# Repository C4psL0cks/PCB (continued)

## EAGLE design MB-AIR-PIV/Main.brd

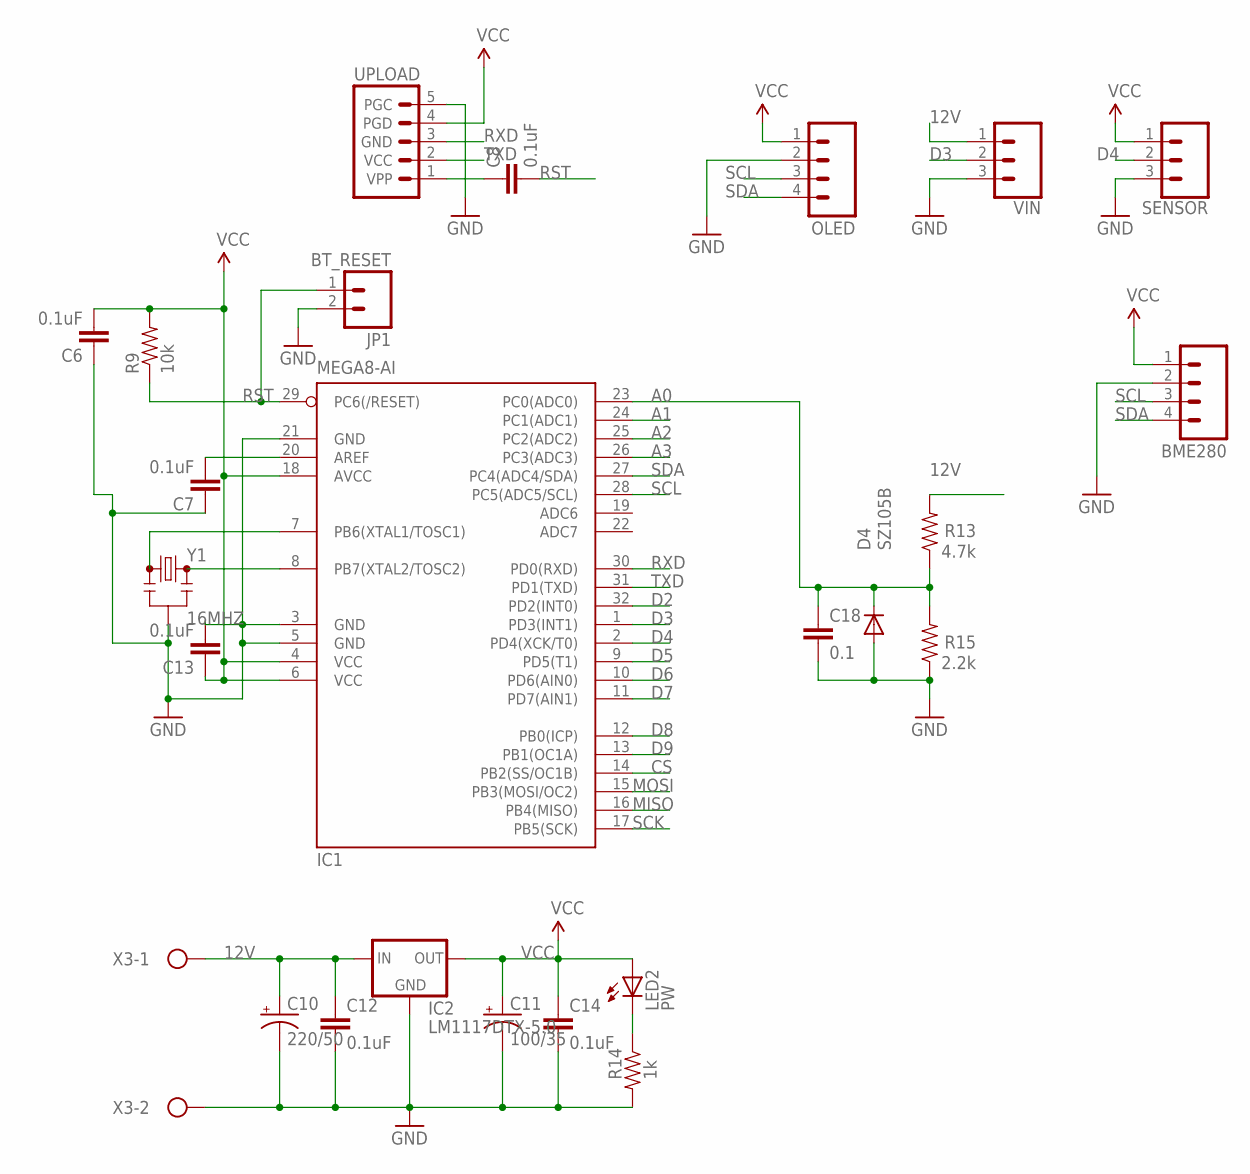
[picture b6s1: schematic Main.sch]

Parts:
BME280: M04PTH; 1X04
C6, C7, C8, C12, C13, C14: 0.1uF; 0805
C10: 220/50; 153CLV-1010
C11: 100/35; 153CLV-0605
C18: 0.1; 0805
D4: SZ105B; DO-214AC
IC1: MEGA8-AI; TQFP32-08
IC2: LM1117DTX-5.0; TO252
JP1: BT_RESET; 1X02
LED2: PW; LED3MM
OLED: M04PTH; 1X04
R9: 10k; 0805
R13: 4.7k; 0805
R14: 1k; 0805
R15: 2.2k; 0805
SENSOR: CONN_03JST-PTH-VERT; JST-3-PTH-VERT
UPLOAD: PIC_ICSP_MINI_5_PIN
VIN: CONN_03JST-PTH-VERT; JST-3-PTH-VERT
X3: RELAY1; W237-102
Y1: 16MHZ; RESONATOR-SMD

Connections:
12V: C10.+, C12.1, IC2.2 (IN), R13.2, VIN.1, X3.1
A0: C18.1, D4.C, IC1.23 (PC0(ADC0)), R13.1, R15.2
A1: IC1.24 (PC1(ADC1))
A2: IC1.25 (PC2(ADC2))
A3: IC1.26 (PC3(ADC3))
CS: IC1.14 (PB2(SS/OC1B))
D2: IC1.32 (PD2(INT0))
D3: IC1.1 (PD3(INT1)), VIN.2
D4: IC1.2 (PD4(XCK/T0)), SENSOR.2
D5: IC1.9 (PD5(T1))
D6: IC1.10 (PD6(AIN0))
D7: IC1.11 (PD7(AIN1))
D8: IC1.12 (PB0(ICP))
D9: IC1.13 (PB1(OC1A))
GND: BME280.2, C6.1, C7.1, C10.-, C11.-, C12.2, C13.2, C14.2, C18.2, D4.A, IC1.3 (GND), IC1.5 (GND), IC1.21 (GND), IC2.1 (GND), JP1.2, OLED.2, R14.2, R15.1, SENSOR.3, UPLOAD.5 (PGC), VIN.3, X3.2, Y1.2
MISO: IC1.16 (PB4(MISO))
MOSI: IC1.15 (PB3(MOSI/OC2))
unnamed: IC1.8 (PB7(XTAL2/TOSC2)), Y1.3
unnamed: IC1.7 (PB6(XTAL1/TOSC1)), Y1.1
unnamed: C7.2, IC1.20 (AREF)
unnamed: C8.1, UPLOAD.1 (VPP)
unnamed: LED2.K (C), R14.1
RST: C8.2, IC1.29 (PC6(/RESET)), JP1.1, R9.1
RXD: IC1.30 (PD0(RXD)), UPLOAD.3 (GND)
SCK: IC1.17 (PB5(SCK))
SCL: BME280.3, IC1.28 (PC5(ADC5/SCL)), OLED.3
SDA: BME280.4, IC1.27 (PC4(ADC4/SDA)), OLED.4
TXD: IC1.31 (PD1(TXD)), UPLOAD.2 (VCC)
VCC: BME280.1, C6.2, C11.+, C13.1, C14.1, IC1.4 (VCC), IC1.6 (VCC), IC1.18 (AVCC), IC2.TAB (OUT), LED2.A, OLED.1, R9.2, SENSOR.1, UPLOAD.4 (PGD)

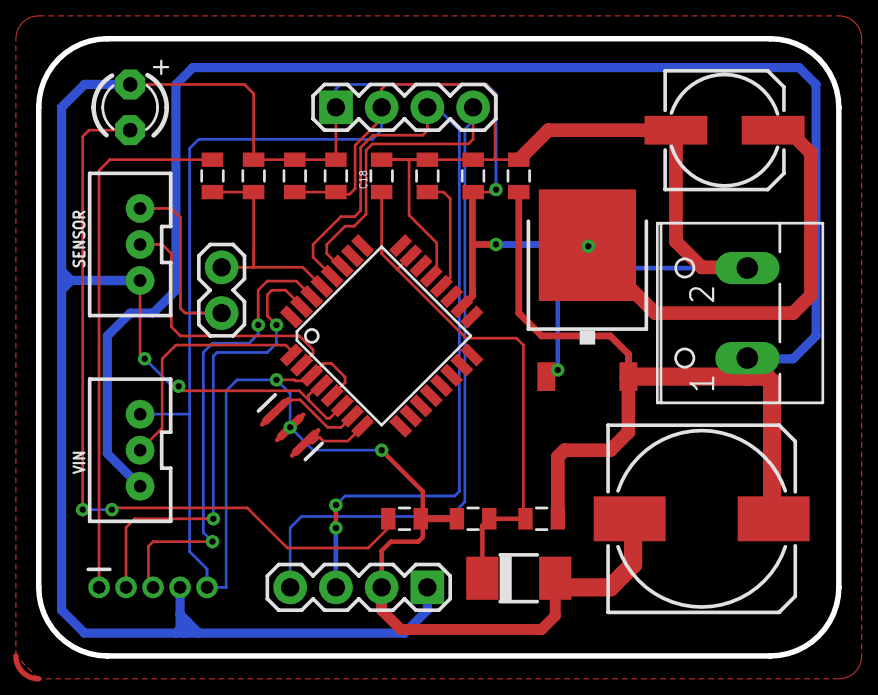
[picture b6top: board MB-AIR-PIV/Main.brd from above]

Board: 2 copper layers, 44.5 x 34.3 mm, 25 parts (0 on the bottom side), 16 nets.

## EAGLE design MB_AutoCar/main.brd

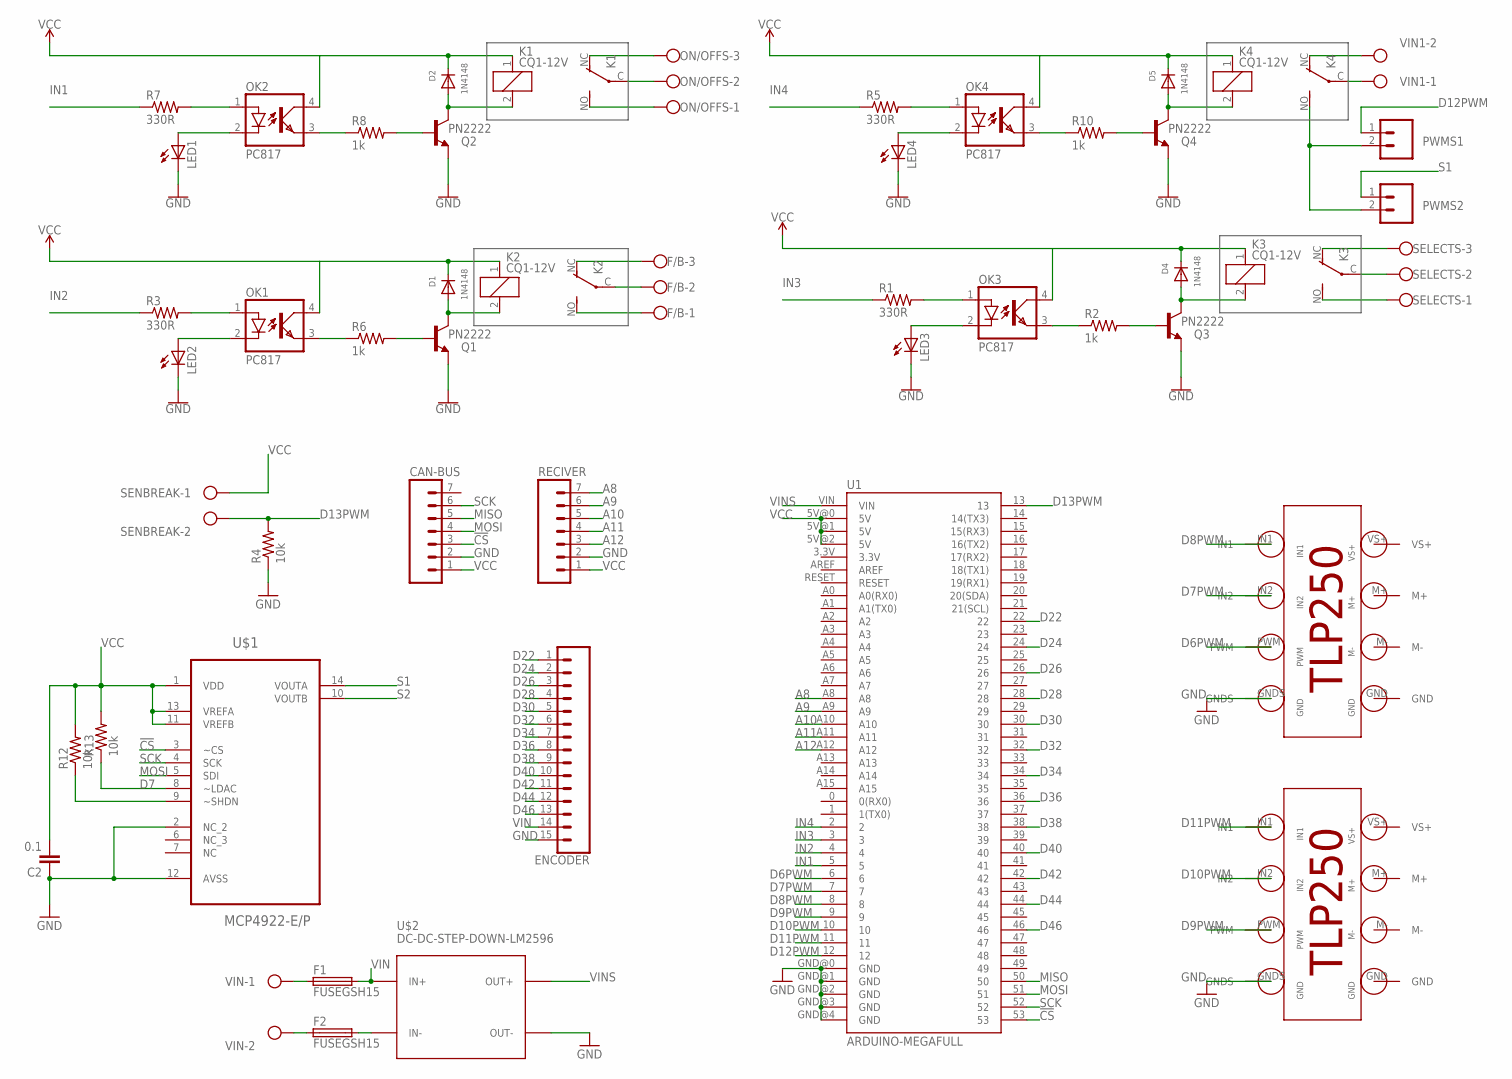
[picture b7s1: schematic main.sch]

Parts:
C2: 0.1; CAP-PTH-5MM
CAN-BUS: M07; 1X07
D1, D2, D4, D5: 1N4148; DO-1N4148
ENCODER: CONN_15; 1X15
F1, F2: FUSEGSH15; GSH15
F/B: W237-103
K1, K2, K3, K4: CQ1-12V; CQ1
LED1, LED2, LED3, LED4: LED3MM
OK1, OK2, OK3, OK4: PC817; DIL04
ON/OFFS: W237-103
PWMS1, PWMS2: Out1; 1X02_LONGPADS
Q1, Q2, Q3, Q4: PN2222; TO92-EBC
R1, R3, R5, R7: 330R; 0204/7
R2, R6, R8, R10: 1k; 0204/7
R4, R12, R13: 10k; AXIAL-0.3
RECIVER: M07; 1X07
SELECTS: W237-103
SENBREAK: Vcc; W237-102
U1: ARDUINO-MEGAFULL; ARDUINO_MEGA
U$1: MCP4922-E/P; DIP254P762X533-14
U$2: DC-DC-STEP-DOWN-LM2596
U$3, U$4: TLP250V1; TLP250
VIN, VIN1: -; W237-102

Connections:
3: D4.A, K3.2, Q3.C
6: D5.A, K4.2, Q4.C
22: D2.A, K1.2, Q2.C
!CS: CAN-BUS.3, U1.53, U$1.3 (~CS)
!SHDN: R12.P$1 (1), U$1.9 (~SHDN)
A8: RECIVER.7, U1.A8
A9: RECIVER.6, U1.A9
A10: RECIVER.5, U1.A10
A11: RECIVER.4, U1.A11
A12: RECIVER.3, U1.A12
D6PWM: U1.6, U$3.PWM
D7PWM: U1.7, U$3.IN2
D8PWM: U1.8, U$3.IN1
D9PWM: U1.9, U$4.PWM
D10PWM: U1.10, U$4.IN2
D11PWM: U1.11, U$4.IN1
D12PWM: PWMS1.1, U1.12
D13PWM: R4.P$2 (2), SENBREAK.2, U1.13
D22: ENCODER.1, U1.22
D24: ENCODER.2, U1.24
D26: ENCODER.3, U1.26
D28: ENCODER.4, U1.28
D30: ENCODER.5, U1.30
D32: ENCODER.6, U1.32
D34: ENCODER.7, U1.34
D36: ENCODER.8, U1.36
D38: ENCODER.9, U1.38
D40: ENCODER.10, U1.40
D42: ENCODER.11, U1.42
D44: ENCODER.12, U1.44
D46: ENCODER.13, U1.46
D48: R13.P$1 (1), U1.48, U$1.8 (~LDAC)
GND: C2.1, CAN-BUS.2, ENCODER.15, LED1.K (C), LED2.K (C), LED3.K (C), LED4.K (C), Q1.E, Q2.E, Q3.E, Q4.E, R4.P$1 (1), RECIVER.2, U1.GND@0 (GND), U1.GND@1 (GND), U1.GND@2 (GND), U1.GND@3 (GND), U1.GND@4 (GND), U$1.2 (NC_2), U$1.12 (AVSS), U$2.OUT-, U$3.GNDS, U$4.GNDS
GND-: D1.A, K2.2, Q1.C
IN1: R7.1, U1.5
IN2: R3.1, U1.4
IN3: R1.1, U1.3
IN4: R5.1, U1.2
INS: OK1.1 (A), R3.2
INSS: OK2.1 (A), R7.2
INSS1: OK3.1 (A), R1.2
INSS2: OK4.1 (A), R5.2
LED: LED2.A, OK1.2 (C)
LEDS: LED1.A, OK2.2 (C)
LEDS1: LED3.A, OK3.2 (C)
LEDS2: LED4.A, OK4.2 (C)
MISO: CAN-BUS.5, U1.50
MOSI: CAN-BUS.4, U1.51, U$1.5 (SDI)
unnamed: K4.NO (S), PWMS1.2, PWMS2.2
unnamed: K1.NO (S), ON/OFFS.1
unnamed: K1.C, ON/OFFS.2
unnamed: F/B.1, K2.NO (S)
unnamed: F/B.2, K2.C
unnamed: Q3.B, R2.2
unnamed: OK3.3 (EMIT), R2.1
unnamed: K3.NO (S), SELECTS.1
unnamed: K3.C, SELECTS.2
unnamed: Q4.B, R10.2
unnamed: OK4.3 (EMIT), R10.1
unnamed: Q1.B, R6.2
unnamed: K4.C, VIN1.1
unnamed: K1.NC (O), ON/OFFS.3
unnamed: F/B.3, K2.NC (O)
unnamed: K3.NC (O), SELECTS.3
unnamed: K4.NC (O), VIN1.2
unnamed: Q2.B, R8.2
unnamed: OK2.3 (EMIT), R8.1
unnamed: F1.1, VIN.1
unnamed: F2.2, U$2.IN-
unnamed: F2.1, VIN.2
OTP: OK1.3 (EMIT), R6.1
S1: PWMS2.1, U$1.14 (VOUTA)
S2: U$1.10 (VOUTB)
SCK: CAN-BUS.6, U1.52, U$1.4 (SCK)
VCC: C2.2, CAN-BUS.1, D1.C, D2.C, D4.C, D5.C, K1.1, K2.1, K3.1, K4.1, OK1.4 (COL), OK2.4 (COL), OK3.4 (COL), OK4.4 (COL), R12.P$2 (2), R13.P$2 (2), RECIVER.1, SENBREAK.1, U1.5V@0 (5V), U1.5V@1 (5V), U1.5V@2 (5V), U$1.1 (VDD), U$1.11 (VREFB), U$1.13 (VREFA)
VIN: ENCODER.14, F1.2, U$2.IN+
VINS: U1.VIN, U$2.OUT+

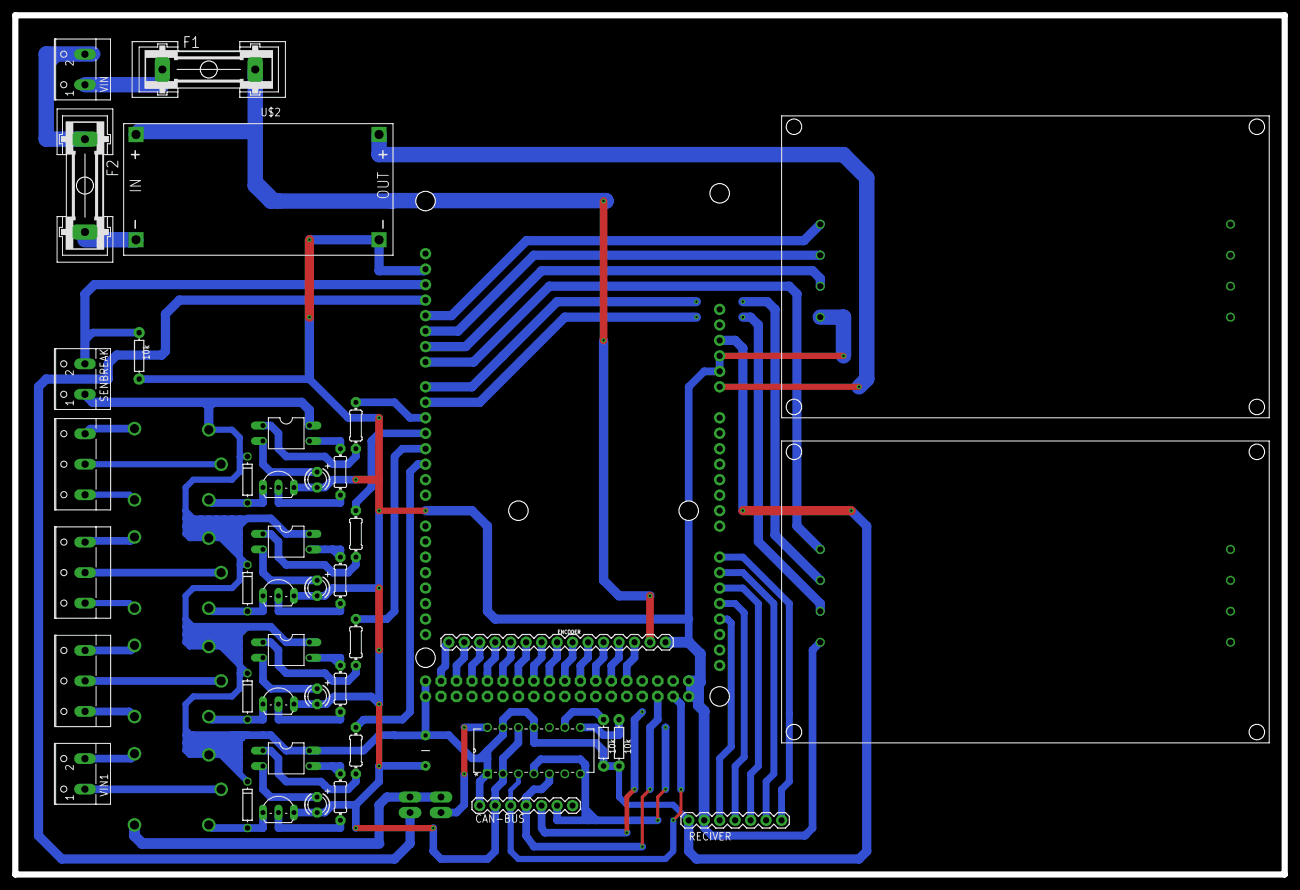
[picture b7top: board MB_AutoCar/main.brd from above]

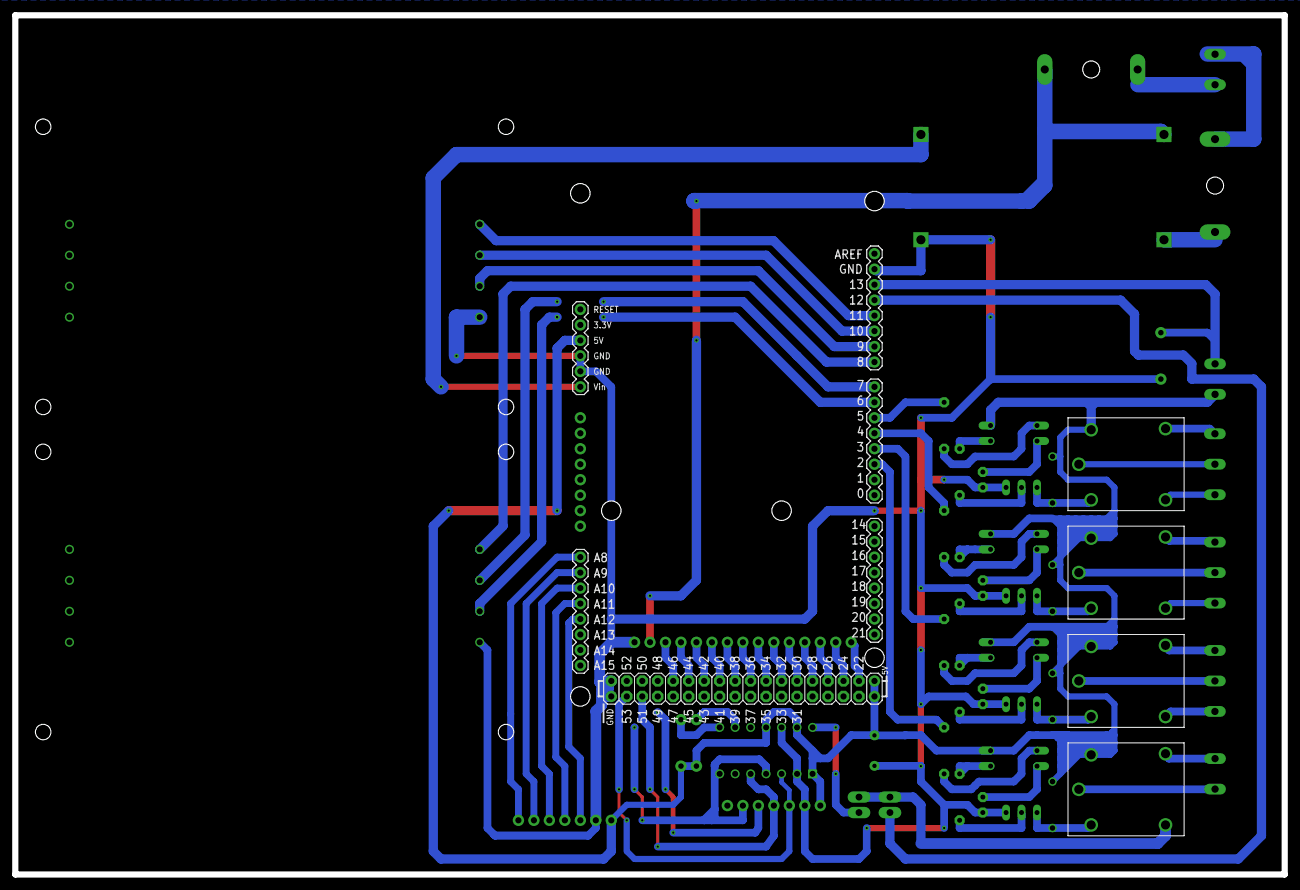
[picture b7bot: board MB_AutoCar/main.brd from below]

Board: 2 copper layers, 208.3 x 141.0 mm, 50 parts (5 on the bottom side), 76 nets.

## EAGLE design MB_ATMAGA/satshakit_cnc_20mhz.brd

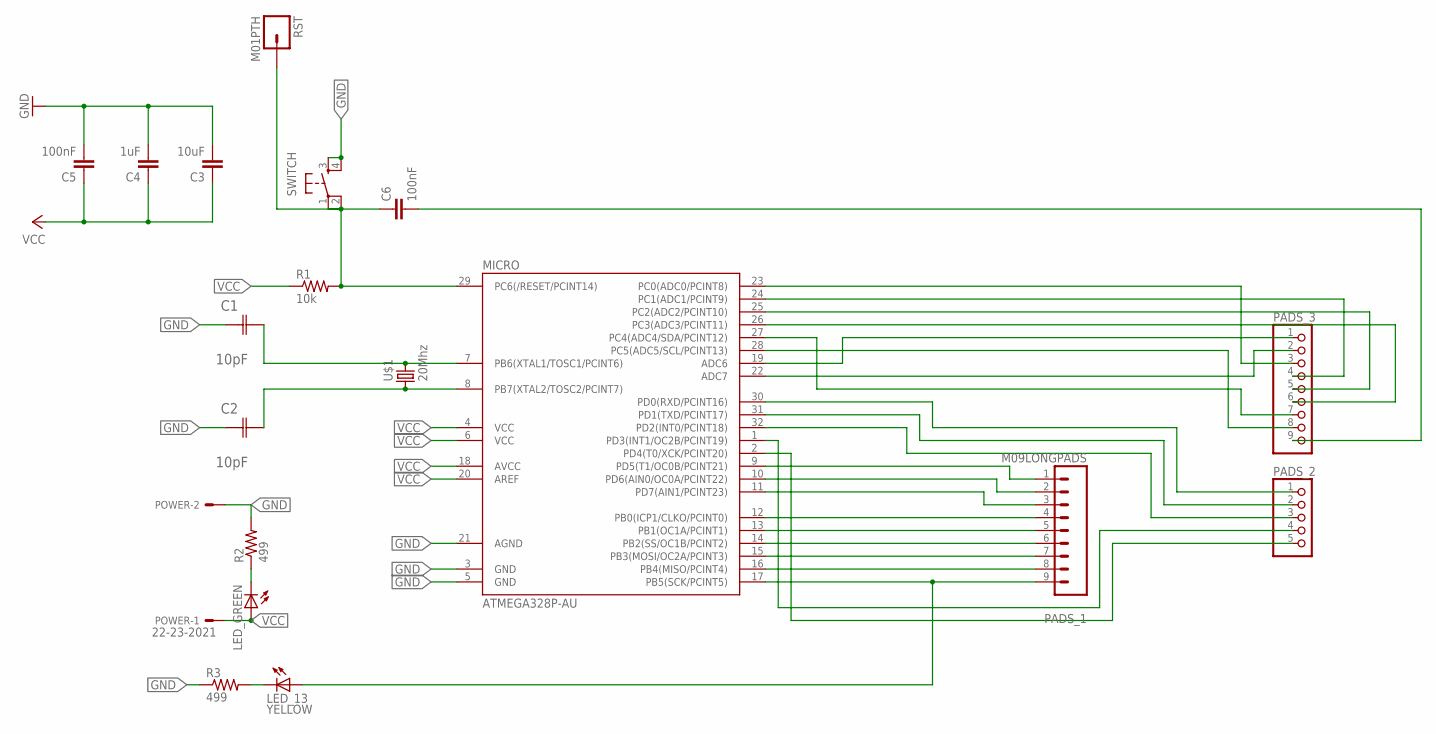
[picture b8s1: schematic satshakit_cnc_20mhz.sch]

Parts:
C1, C2: 10pF; CAPC3216X178N
C3: 10uF; 1206
C4: 1uF; 1206
C5, C6: 100nF; 1206
LED_13: YELLOW; 1206
LED_GREEN: LED1206; 1206
MICRO: ATMEGA328P-AU; TQFP32-08
PADS_1: M09LONGPADS; 1X09_LONGPADS
PADS_2: PINHD-1X5; 1X05
PADS_3: PINHD-1X9; 1X09
POWER: 22-23-2021
R1: 10k; 1206
R2, R3: 499; 1206
RST: M01PTH; 1X01
SWITCH: 6MM_SWITCH6MM_SWITCH; 6MM_SWITCH
U$1: 20Mhz; 2-SMD-5X3MM

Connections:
GND: C1.1 (C1), C2.1 (C1), C3.2, C4.2, C5.2, MICRO.3 (GND), MICRO.5 (GND), MICRO.21 (AGND), POWER.2, R2.2, R3.1, SWITCH.3 (S), SWITCH.4 (S1)
unnamed: MICRO.9 (PD5(T1/OC0B/PCINT21)), PADS_1.1
unnamed: C1.2 (C2), MICRO.7 (PB6(XTAL1/TOSC1/PCINT6)), U$1.P$2 (2)
unnamed: C6.2, PADS_3.9
unnamed: MICRO.10 (PD6(AIN0/OC0A/PCINT22)), PADS_1.2
unnamed: MICRO.11 (PD7(AIN1/PCINT23)), PADS_1.3
unnamed: MICRO.12 (PB0(ICP1/CLKO/PCINT0)), PADS_1.4
unnamed: MICRO.13 (PB1(OC1A/PCINT1)), PADS_1.5
unnamed: MICRO.14 (PB2(SS/OC1B/PCINT2)), PADS_1.6
unnamed: C2.2 (C2), MICRO.8 (PB7(XTAL2/TOSC2/PCINT7)), U$1.P$1 (1)
unnamed: MICRO.15 (PB3(MOSI/OC2A/PCINT3)), PADS_1.7
unnamed: MICRO.16 (PB4(MISO/PCINT4)), PADS_1.8
unnamed: LED_13.1 (A), MICRO.17 (PB5(SCK/PCINT5)), PADS_1.9
unnamed: MICRO.19 (ADC6), PADS_3.1
unnamed: MICRO.22 (ADC7), PADS_3.2
unnamed: MICRO.23 (PC0(ADC0/PCINT8)), PADS_3.3
unnamed: MICRO.24 (PC1(ADC1/PCINT9)), PADS_3.4
unnamed: MICRO.25 (PC2(ADC2/PCINT10)), PADS_3.5
unnamed: MICRO.26 (PC3(ADC3/PCINT11)), PADS_3.6
unnamed: MICRO.27 (PC4(ADC4/SDA/PCINT12)), PADS_3.7
unnamed: MICRO.30 (PD0(RXD/PCINT16)), PADS_2.1
unnamed: MICRO.31 (PD1(TXD/PCINT17)), PADS_2.2
unnamed: MICRO.32 (PD2(INT0/PCINT18)), PADS_2.3
unnamed: MICRO.1 (PD3(INT1/OC2B/PCINT19)), PADS_2.4
unnamed: MICRO.2 (PD4(T0/XCK/PCINT20)), PADS_2.5
unnamed: MICRO.28 (PC5(ADC5/SCL/PCINT13)), PADS_3.8
unnamed: LED_GREEN.2 (C), R2.1
unnamed: LED_13.2 (C), R3.2
unnamed: C6.1, MICRO.29 (PC6(/RESET/PCINT14)), R1.2, RST.1, SWITCH.1, SWITCH.2 (P1)
VCC: C3.1, C4.1, C5.1, LED_GREEN.1 (A), MICRO.4 (VCC), MICRO.6 (VCC), MICRO.18 (AVCC), MICRO.20 (AREF), POWER.1, R1.1

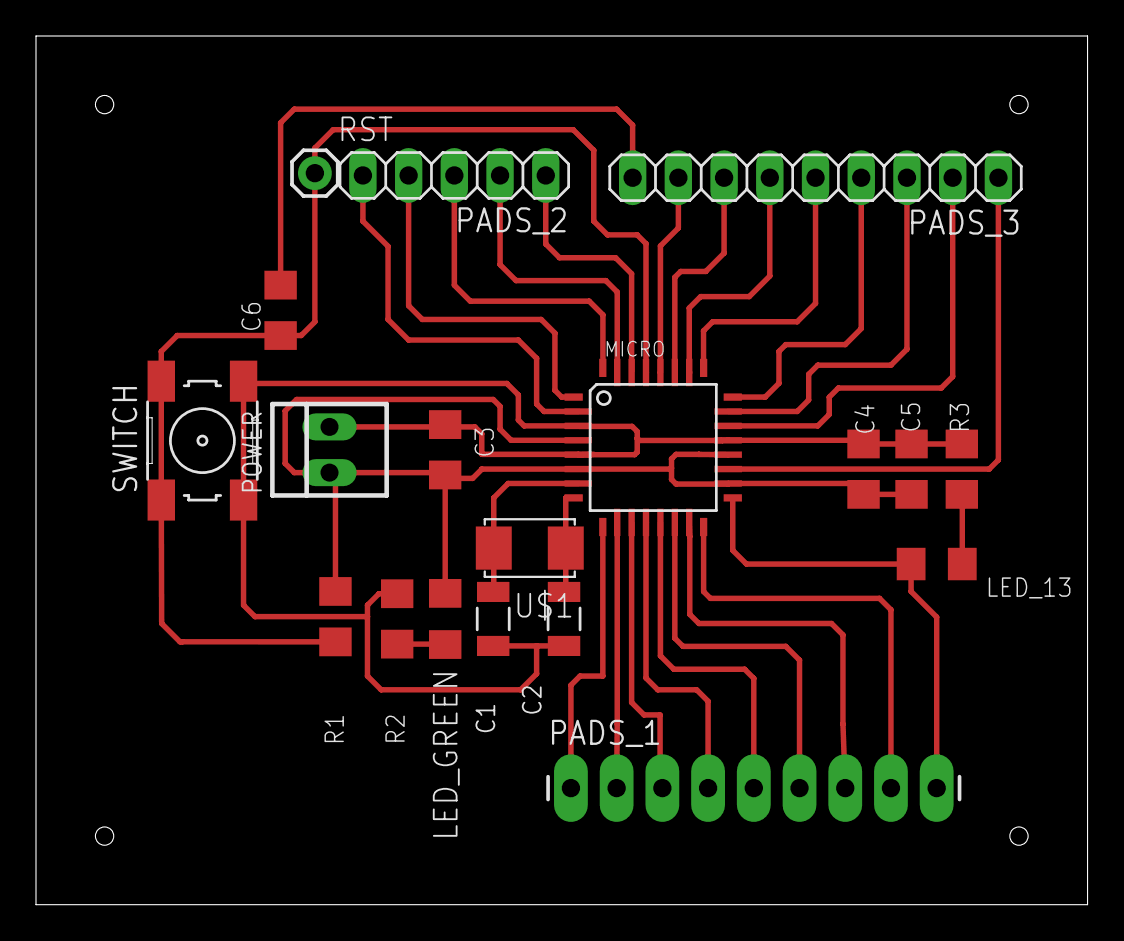
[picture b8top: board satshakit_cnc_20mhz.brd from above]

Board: 2 copper layers, 58.4 x 48.3 mm, 19 parts (0 on the bottom side), 30 nets.

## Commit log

2020-09-14 add new pcb all
2020-09-18 add new nfr
2020-09-18 add license
2020-09-22 add NEW
2020-09-29 add new mb
2020-09-29 edit file
2020-10-21 new pwm
